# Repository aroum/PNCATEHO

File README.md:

<p align="center">
  <a href="https://github.com/aroum/PNCATEHO/tree/master/firmware">Firmware | </a>
  <a href="https://github.com/aroum/PNCATEHO/releases">Gerber | </a>
  <a href="../doc/socket.md">About socket</a>
</p>

---

## About

РИСАТЕНО (__RISATENO__) - created as a rethinking of [ARTSEY](https://artsey.io/) for the Russian language. 10 keys, two for each finger. The name is made up of letters on the main layer. The letters on the base layer are selected according to the. The original idea was to create a compact keyboard for chord typing, but it can also be used as a macro pad. When using two halves of РИСАТЕНО connected via Bluetooth, you can use the [Kladenets layout](https://ibnteo.github.io/kladenets/). But over time, PNCATEHO became something more. It is a synthesizer, a sampler, a MIDI keyboard, and a vast playground for your other experiments.

## Eras

Eras are a way to classify different versions of a project. The Stone Era reflects original ideas. The Glass Era reflects the community's desires and experiments with new switches. The Light Era illuminates the vision of the creators who use this project as a platform for professional growth and attempt what others were afraid to do.

| Name    | Alt Name  | Era   | Swtiches   | Hot-swap | LED              | Wireless | MCU           |
| ------- | --------- | ----- | ---------- | -------- | ---------------- | -------- | ------------- |
| V4      | -         | Stone | Choc V1    | ❌        | Per-key          | Optional | proMicro like |
| V5      | -         | Glass | Choc V1/V2 | ✅        | Per-key          | Optional | proMicro like |
| MK_Dose | Dozateno  | Glass | MK Dose/MX | ✅        | 3 Led indication | Optional | proMicro like |
| Welcome | Nizkoteno | Light | PG1316S    | ❌<br>    | Per-key          | ❌<br>    | rp2040        |

### Stone

The standard version of PNCATEHO from the Stone era. Supports per-key backlighting, the option to use a wireless controller with an external power switch and reset button, and an open case. It does not support hot-swapping switches and only supports Choc V1. [more about stone](stone/readme.md)

> [!WARNING]  
> In version 0.3 of the board there is a bug with the backlight on the right-hand half.

#### V0.3

#### 3D

### Glass

The modern era of PNCATEHO development. It differs from the Stone era in that it supports hot-swappable keys and ChocV1/V2, MK Dose, and MX switches. It also uses closed cases and a new design approach by turtle_bazon. [more about Glass](glass/readme.md)

> [!TIP]
> If you want to build a PNCATEHO with MX switches, you can use the PCB from MK Dose.

#### V5

#### MK_Dose

### Light

This is an era where the controller is soldered directly onto the PCB, exploring various form factors such as, for example, a PNCATEHO the size of a card. A project can become a flashlight, a development board, or even a portable gaming console. It all depends on the imagination of the community. The main contribution to this era has been made by the authors of the inpudiy community. [more about light](light/readme.md)

#### Welcome

## FAQ

### What is it for?

First and foremost, PNCATEHO is a fun project. It shouldn't be treated as an everyday keyboard—it’s more of a novelty, like a fridge magnet. That said, some people actually try to apply PNCATEHO's concepts to their daily-driver keyboards.

In many ways, the project served as a testing ground for experimenting with chording and exploring just how far you can minimize the number of keys. Of course, nothing stops you from using PNCATEHO as a macropad. There are also firmwares available to turn PNCATEHO into a sampler, synthesizer, or MIDI keyboard.

I wanted to design a layout that was simple and intuitive, yet still capable of acting as a near-full replacement for a standard keyboard. Unlike ARTSEY, I don’t use chords that require pressing more than two keys simultaneously. I also designed the layout based on letter frequency rather than just picking pleasant-sounding combinations. On top of that, I added two thumb keys—it felt odd to allocate two keys for every other finger while leaving the thumbs with nothing.

### Why PNCATEHO/RISATENO/РИСАТЕНО?

PNCATEHO is a loose transliteration of the Russian word "РИСАТЕНО" (RISATENO) into the Latin alphabet. The layout was designed based on letter frequency ([Wikipedia](https://ru.wikipedia.org/wiki/%D0%A7%D0%B0%D1%81%D1%82%D0%BE%D1%82%D0%BD%D0%BE%D1%81%D1%82%D1%8C)), where the first eight letters are four vowels ('И', 'А', 'Е', 'О') and four consonants ('Р', 'С', 'Т', 'Н'). To create a pronounceable name, they can be grouped into syllables: reading them one way gives __RISATENO__, and the other way gives __NOTESARI__ (options like "ONETASIR" were discarded as awkward-sounding). The second option felt a bit too "samurai," so I went with the first.

As a nice bonus, if you set aside the Cyrillic letter "И", the name transliterates perfectly into the Latin alphabet, and the letter "N" works great as a visual substitute for "И".

### Why no ergonomic stagger?

PNCATEHO was never meant to be an everyday keyboard—aesthetics take priority over ergonomics here, and in my opinion, ortholinear layouts look much cleaner. Besides, when you only have two keys per finger, column-staggering doesn't really make much of a difference anyway.

### How do you type on it?

Letter by letter, “dancing” your fingers to form chords. I tried to distribute chords by ease of pressing, so that the most common symbols use the simplest and most comfortable combinations. With some effort, you can learn all the common chords in a couple of days and, although slowly, fully type using just 10 keys with one hand.

It’s quite an unusual experience, especially if you’ve never used chords before. I strongly recommend printing the layout ([GitHub](https://github.com/aroum/PNCATEHO/tree/master/firmware)) and opening any beginner touch-typing app — even if you already know how to type on a regular keyboard, this will be a completely new and unique experience that you’ll likely never need anywhere else.

### Is this steno?

No, steno works completely differently ([example layout](https://github.com/openstenoproject/plover/files/247728/Russian.alphabet.and.layout.pdf)). It requires more keys and a different method. PNCATEHO, on the other hand, is letter-by-letter input based on frequency.

If you’re interested in steno, it’s worth starting with [Plover](https://www.openstenoproject.org/plover/).

## Inspiration

* [ARTSEY](https://artsey.io/)
* [The Paintbrush](https://github.com/artseyio/thepaintbrush)
* [Helix](https://github.com/MakotoKurauchi/helix)
* [wakizashi](https://klava.wiki/hypha/%D0%BA%D0%BB%D0%B0%D0%B2%D0%B8%D0%B0%D1%82%D1%83%D1%80%D1%8B/%D0%B2%D0%B0%D0%BA%D0%B8%D0%B4%D0%B7%D0%B0%D1%81%D0%B8) (saw after the release of PNCATEHO)

## Contribute list

* [aroum](https://github.com/aroum)
* [mayoroffk](https://github.com/mayoroffk)
* [turtle-bazon](https://github.com/turtle-bazon)
* [miwoho](https://github.com/miwoho)

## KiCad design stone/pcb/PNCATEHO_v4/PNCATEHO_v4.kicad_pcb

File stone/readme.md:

# STONE

The standard version of PNCATEHO from the Stone era. Supports per-key backlighting, the option to use a wireless controller with an external power switch and reset button, and an open case. It does not support hot-swapping switches and only supports Choc V1.

<p align="center">
  <a href="case/case_v4.stp">Case | </a>
  <a href="build.md">Build Guide</a>
</p>

## V0.3

### Features

* 10 keys, Kailh Choc V1 switches
* Choc spacing
* Direct pins
* Three mounting screws
* One PCB for right and left versions
* Wireless (optional)
* Per switch RGB (optional)
* Power switch for wireless controllers (optional)
* Two halves placed on one 100x100mm pcb (optional)

### PCB

There are several versions of the PCB. In version 0.3, the right half has an error in the LED footprints, so the backlighting can only be installed facing downward. This issue, along with other minor ones, was fixed in version 0.4.

For manufacturing, it is recommended to use 100×100 mm Gerber files. This way, 5 boards become 10 halves (5 right and 5 left).

### Case

In the case directory, there are two STEP files. case_v4.stp does not have cutouts for rubber feet, while case_v4_flex.stp includes 7 cutouts for rubber feet.

### Plate

No plate is needed for choc, but if you want you can order PCB or laser cut. These don't fit version 3 boards because you can't add screw cutouts.

### BOM

| Item                 | Quantity | Remarks                            |
| -------------------- | -------: | ---------------------------------- |
| nice!nano            |        1 | or any other compatible controller |
| Kailh Choc V1        |       10 | switches                           |
| Keycaps              |       10 | 1U                                 |
| YS-SK6812MINI-E      |       10 | RGB leds                           |
| Magnets              |      2-6 | disc 7x2 mm (for case)             |
| Sockets PH5.0mm      |     12x2 | for controller                     |
| SMD button 3x4x2mm   |        1 | for reset                          |
| MSK-12C02            |        1 | power switch  (wireless only)      |
| 301230 3.7v li-po    |        1 | battery  (wireless only)           |
| Silicone rubber feet |        7 | 5x2 mm                             |
| M2 nuts              |        3 | for case v3+                       |
| M2x4 sqrews          |        3 | for case v3+                       |

## 3D

### Case

The case folder contains a STEP file. The controller, circuitry, and mounting method are entirely up to you.

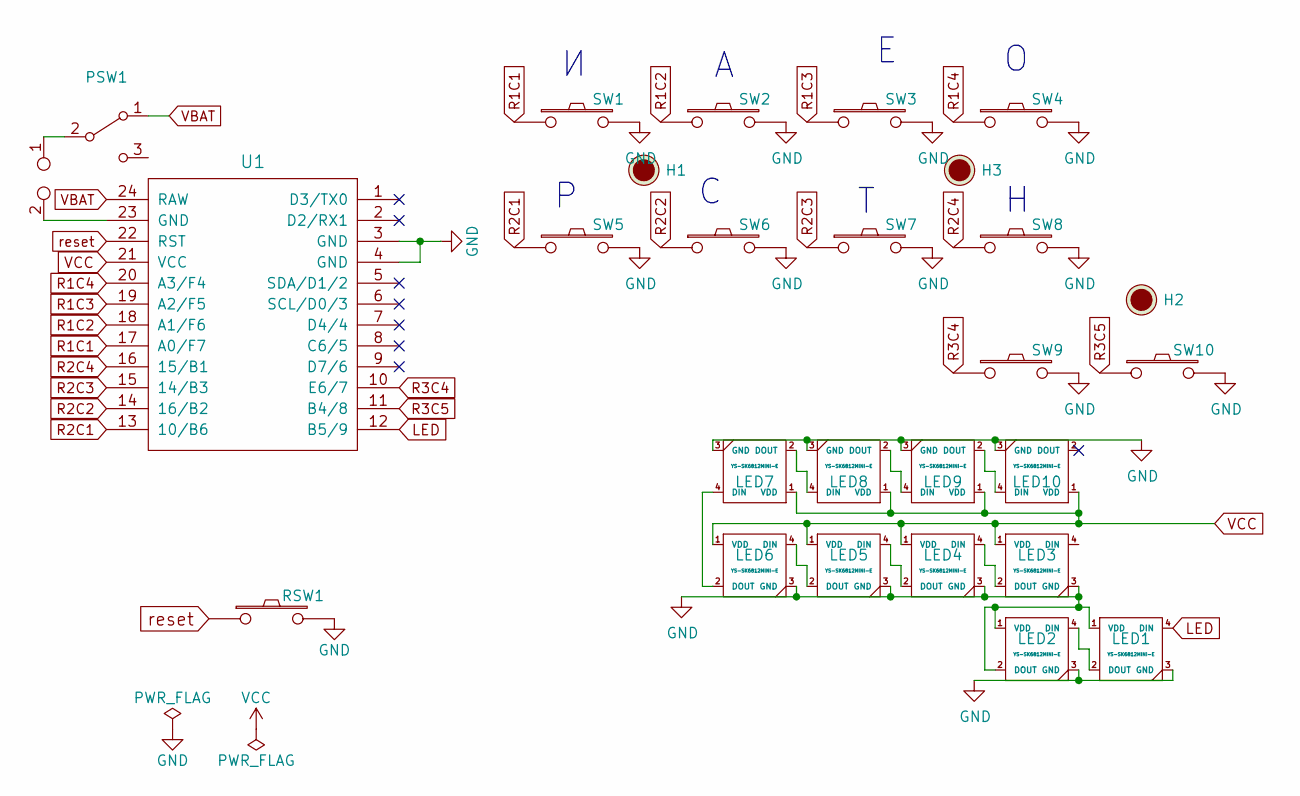
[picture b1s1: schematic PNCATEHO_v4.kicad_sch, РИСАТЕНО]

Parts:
H1, H2, H3: Hole; HOLE
J1: TestPoint_2Pole; battery_conn
LED1, LED2, LED3, LED4, LED5, LED6, LED7, LED8, LED9, LED10: YS-SK6812MINI-E; YS-SK6812MINI-E_duplex
PSW1: SW_SPDT; switch_MSK-12C02_smd
RSW1: SW_PUSH; SW_3x4x2_2legs_duplex
SW1, SW2, SW3, SW4, SW5, SW6, SW7, SW8, SW9, SW10: SW_PUSH; ChocV1_duplex
U1: ProMicro_r; ProMicro_duplex

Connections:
GND: LED1.1 (VDD), LED1.3 (GND), LED2.1 (VDD), LED2.2 (DOUT), LED2.3 (GND), LED3.3 (GND), LED4.3 (GND), LED5.3 (GND), LED6.3 (GND), LED7.3 (GND), LED8.3 (GND), LED9.3 (GND), LED10.3 (GND), RSW1.2, SW1.2, SW2.2, SW3.2, SW4.2, SW5.2, SW6.2, SW7.2, SW8.2, SW9.2, SW10.2, U1.3 (GND), U1.4 (GND)
LED: LED1.4 (DIN), U1.12 (B5/9)
unnamed: J1.2, U1.23 (GND)
unnamed: LED1.2 (DOUT), LED2.4 (DIN)
unnamed: LED3.2 (DOUT), LED4.4 (DIN)
unnamed: LED4.2 (DOUT), LED5.4 (DIN)
unnamed: LED5.2 (DOUT), LED6.4 (DIN)
unnamed: LED6.2 (DOUT), LED7.4 (DIN)
unnamed: LED7.2 (DOUT), LED8.4 (DIN)
unnamed: LED8.2 (DOUT), LED9.4 (DIN)
unnamed: LED9.2 (DOUT), LED10.4 (DIN)
unnamed: J1.1, PSW1.2 (B)
R1C1: SW1.1, U1.17 (A0/F7)
R1C2: SW2.1, U1.18 (A1/F6)
R1C3: SW3.1, U1.19 (A2/F5)
R1C4: SW4.1, U1.20 (A3/F4)
R2C1: SW5.1, U1.13 (10/B6)
R2C2: SW6.1, U1.14 (16/B2)
R2C3: SW7.1, U1.15 (14/B3)
R2C4: SW8.1, U1.16 (15/B1)
R3C4: SW9.1, U1.10 (E6/7)
R3C5: SW10.1, U1.11 (B4/8)
VBAT: PSW1.1 (A), U1.24 (RAW)
VCC: LED3.1 (VDD), LED4.1 (VDD), LED5.1 (VDD), LED6.1 (VDD), LED7.1 (VDD), LED8.1 (VDD), LED9.1 (VDD), LED10.1 (VDD), U1.21 (VCC)
reset: RSW1.1, U1.22 (RST)

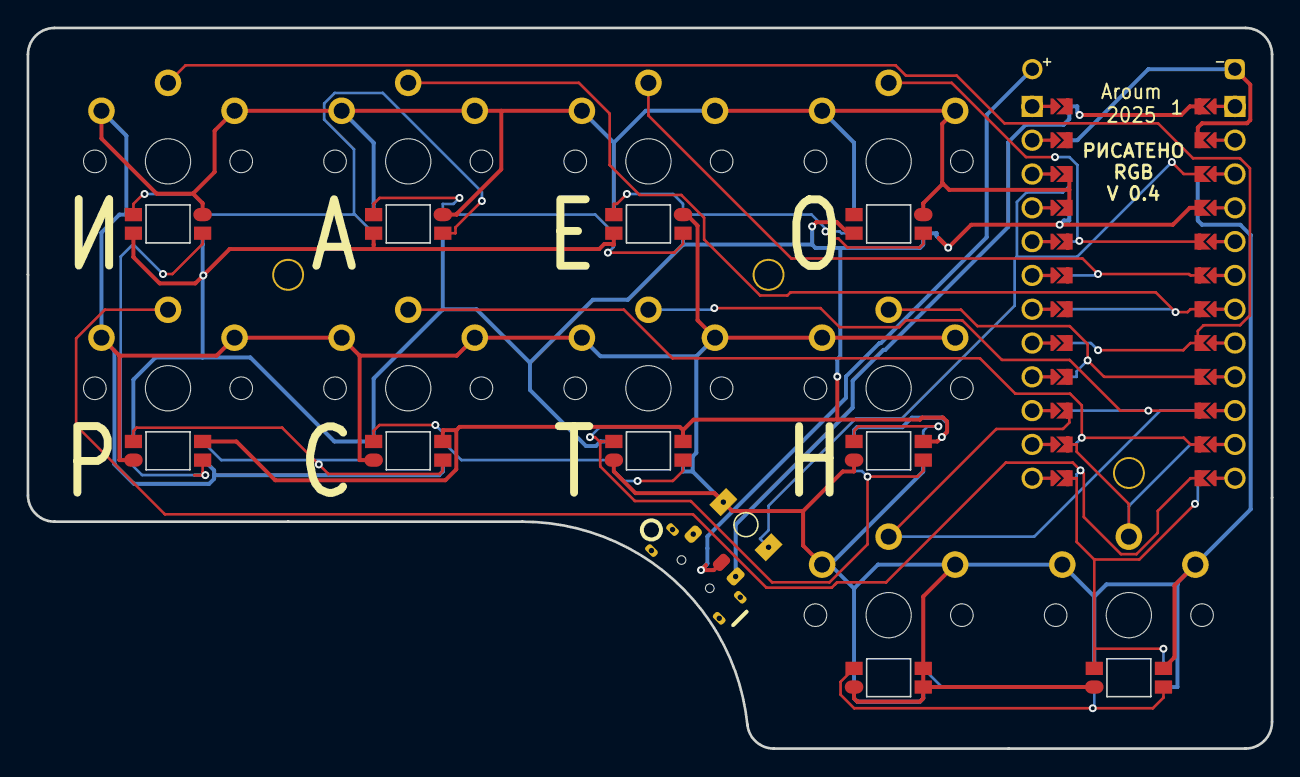
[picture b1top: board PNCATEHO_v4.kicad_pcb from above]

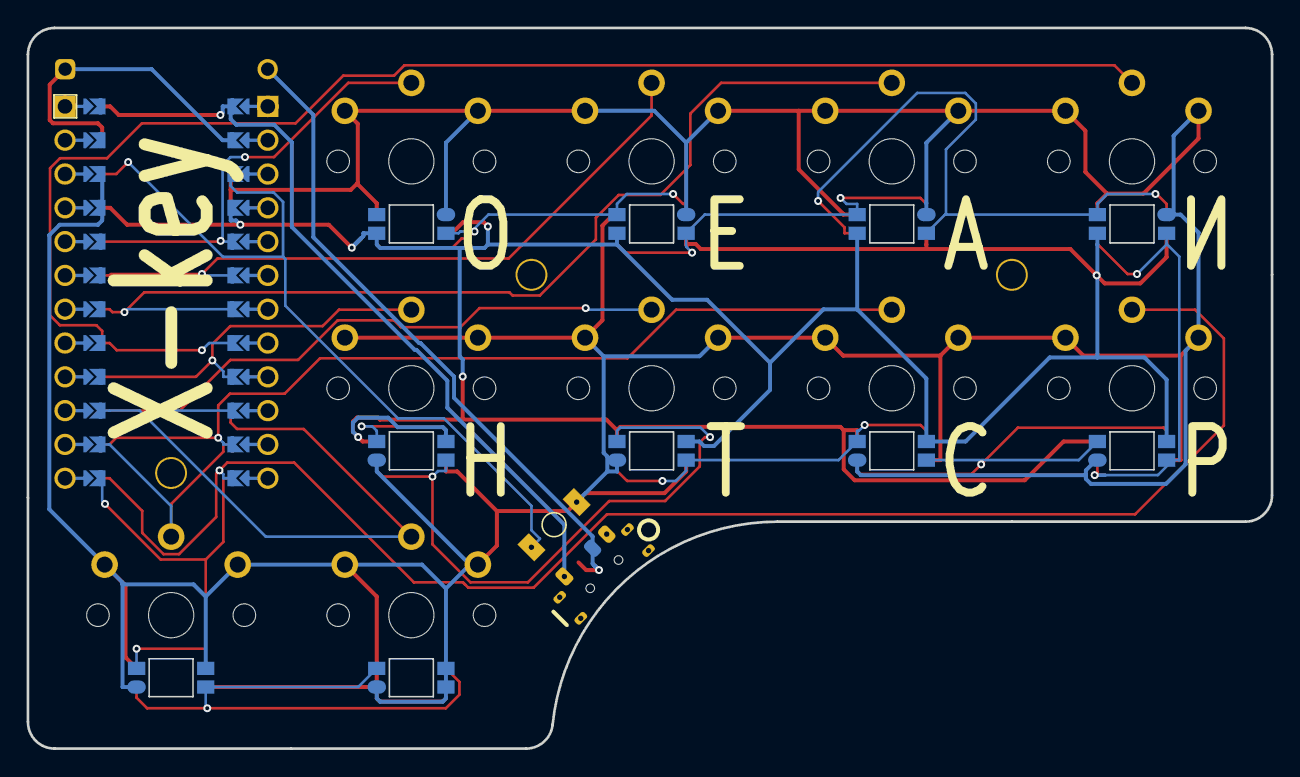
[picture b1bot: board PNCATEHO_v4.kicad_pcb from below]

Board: 2 copper layers, 93.5 x 54.1 mm, 27 parts (10 on the bottom side), 25 nets.

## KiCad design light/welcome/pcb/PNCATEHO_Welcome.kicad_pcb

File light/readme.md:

# light

This is an era where the controller is soldered directly onto the PCB, exploring various form factors such as, for example, a PNCATEHO the size of a card. A project can become a flashlight, a development board, or even a portable gaming console. It all depends on the imagination of the community. The main contribution to this era has been made by the authors of the inpudiy community.

## welcome (nizkoteno)

A credit card–sized RP2040-based PCB with a clean design, PG1316 low-profile switches, and integrated per-key RGB lighting.

<p align="center">
  <a href="https://htmlpreview.github.io/?https://github.com/inpudiy/PNCATEHO/blob/master/light/welcome/doc/ibom.html" style="text-decoration: none;">IBOM |</a>
  <a href="welcome/doc/schematic.pdf" style="text-decoration: none;"> Schematic PDF | </a>
  <a href="welcome/doc/build.md" style="text-decoration: none;"> Build guide</a>
</p>

### Features

* 10 low profile keys, PG1316 switches
* Debit card dimensions (ISO/IEC 7810 ID-1)
* Per switch WS2812 2020 led
* Soldered directly onto the RP2040 board
* ESD protection
* 16 MB flash memory
* cutout for a strap
* exposed 10-pin JST connector for connecting modules

### PCB

The current PCB version is v1.1. For ordering, specify a board thickness of 1.6 mm and a stencil for the top side of the board.

### JST

A BM10B-SRSS-TB connector is installed on the board. This is a 10-pin JST connector with a 1 mm pitch. The leftmost pin is connected to ground, and the rightmost pin provides 3.3V. Between them, the following GPIOs are exposed: 29, 28, 27, 26, 24, 21, 20, 19.

To run the controller, a stable 3.3V supply is required, while the RGB pins should receive 5V.

> [!WARNING]  
> DO NOT attempt to connect an external 3.3V supply while simultaneously powering the board via USB.

### Firmwares

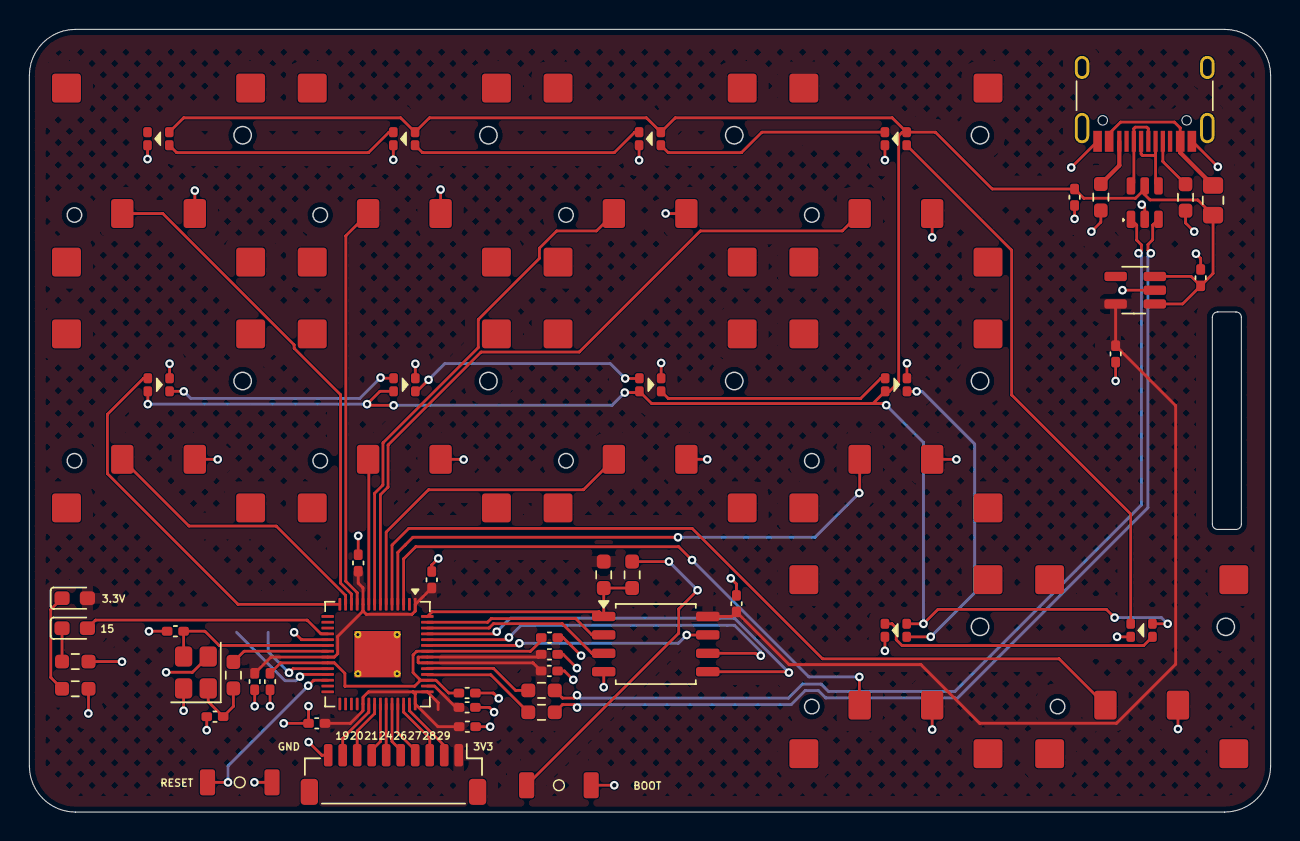
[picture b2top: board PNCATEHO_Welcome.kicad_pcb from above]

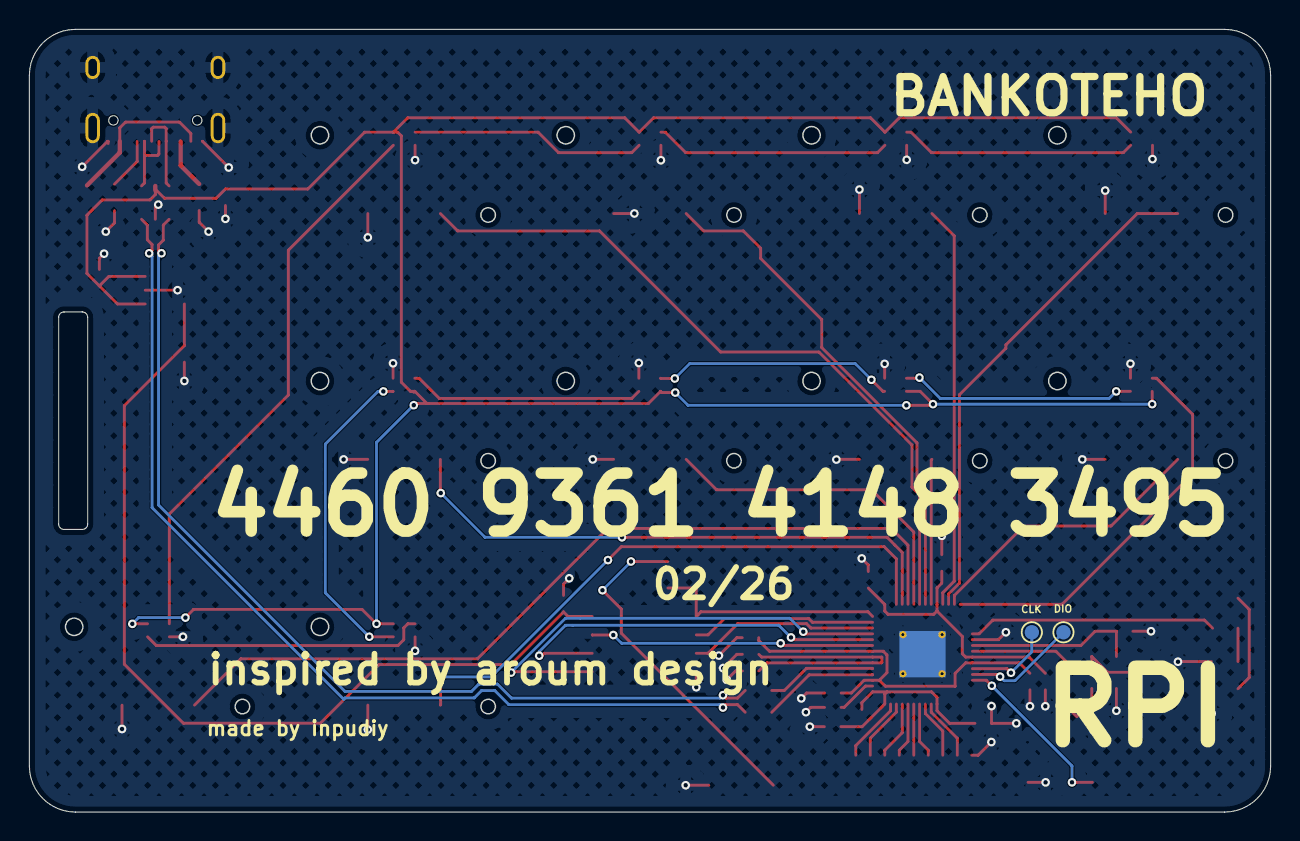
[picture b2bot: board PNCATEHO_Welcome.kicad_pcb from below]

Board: 2 copper layers, 85.6 x 54.0 mm, 60 parts (2 on the bottom side), 57 nets.

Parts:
C1, C2, C13, C16: 1uF; C_0402_1005Metric_Pad0.74x0.62mm_HandSolder
C3, C6, C7, C8, C9, C10, C11, C12, C14, C15, C17: 100nF; C_0402_1005Metric_Pad0.74x0.62mm_HandSolder
C4, C5: 15pF; C_0402_1005Metric_Pad0.74x0.62mm_HandSolder
D1: RED; LED_0603_1608Metric_Pad1.05x0.95mm_HandSolder
D2: BLUE; LED_0603_1608Metric_Pad1.05x0.95mm_HandSolder
D3, D4, D5, D6, D7, D8, D9, D10, D11, D12: LED-SMD_4P-L2.0-W1.8_XL-0807RGBC-WS2812B
F1: 0.5А 6V; Fuse_0805_2012Metric_Pad1.15x1.40mm_HandSolder
J1: USB_C_Receptacle_USB2.0; USB_C_Receptacle_HRO_TYPE-C-31-M-12
J2: Conn_01x10; JST_SH_BM10B-SRSS-TB_1x10-1MP_P1.00mm_Vertical
R1, R2: 5.1k; R_0603_1608Metric_Pad0.98x0.95mm_HandSolder
R3, R4, R9, R10: 1k; R_0603_1608Metric_Pad0.98x0.95mm_HandSolder
R5: 10k; R_0603_1608Metric_Pad0.98x0.95mm_HandSolder
R6, R7: 27; R_0603_1608Metric_Pad0.98x0.95mm_HandSolder
SW1, SW2, SW3, SW4, SW5, SW6, SW7, SW8, SW9, SW10: CPG1316S01D02-01
SW11: Boot; TS342A2P
SW12: Reset; TS342A2P
TP1, TP2: TestPoint; TestPoint_Pad_D1.0mm
U1: RP2040; QFN-56-1EP_7x7mm_P0.4mm_EP3.2x3.2mm_ThermalVias
U2: RT9013-33GB; SOT-23-5_HandSoldering
U3: W25Q128JVS; SOIC-8_5.3x5.3mm_P1.27mm
U4: USBLC6-2SC6; SOT23-6L
Y1: 12MHz; Crystal_SMD_Abracon_ABM8G-4Pin_3.2x2.5mm

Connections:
+1V1: C14.1, C15.1, C16.1, U1.23 (DVDD), U1.45 (VREG_VOUT), U1.50 (DVDD)
+3V3: C2.1, C3.1, C6.1, C7.1, C8.1, C9.1, C10.1, C11.1, C12.1, C13.1, D1.2 (A), J2.1, R5.2, U1.1 (IOVDD), U1.10 (IOVDD), U1.22 (IOVDD), U1.33 (IOVDD), U1.42 (IOVDD), U1.43 (ADC_AVDD), U1.44 (VREG_IN), U1.48 (USB_VDD), U1.49 (IOVDD), U2.5 (VOUT), U3.8 (VCC)
+5V: C1.1, C17.2, D3.4 (VDD), D4.4 (VDD), D5.4 (VDD), D6.4 (VDD), D7.4 (VDD), D8.4 (VDD), D9.4 (VDD), D10.4 (VDD), D11.4 (VDD), D12.4 (VDD), F1.2, U2.1 (VIN), U2.3 (EN), U4.5 (VBUS)
BOOT: R4.2, SW11.2
GND: C1.2, C2.2, C3.2, C4.2, C5.2, C6.2, C7.2, C8.2, C9.2, C10.2, C11.2, C12.2, C13.2, C14.2, C15.2, C16.2, C17.1, D3.2 (GND), D4.2 (GND), D5.2 (GND), D6.2 (GND), D7.2 (GND), D8.2 (GND), D9.2 (GND), D10.2 (GND), D11.2 (GND), D12.2 (GND), J1.A1 (GND), J1.A12 (GND), J1.B1 (GND), J1.B12 (GND), J1.S1 (SHIELD), J2.10, R1.2, R2.2, R9.1, R10.1, SW1.2, SW2.2, SW3.2, SW4.2, SW5.2, SW6.2, SW7.2, SW8.2, SW9.2, SW10.2, SW11.1, SW12.1, U1.19 (TESTEN), U1.57 (GND), U2.2 (GND), U3.4 (GND), U4.2 (GND), Y1.2, Y1.4
GPIO19: J2.9, U1.34 (GPIO22)
GPIO20: J2.8, U1.35 (GPIO23)
GPIO21: J2.7, U1.36 (GPIO24)
GPIO24: J2.6, U1.37 (GPIO25)
GPIO26: J2.5, U1.38 (GPIO26_ADC0)
GPIO27: J2.4, U1.39 (GPIO27_ADC1)
GPIO28: J2.3, U1.40 (GPIO28_ADC2)
GPIO29: J2.2, U1.41 (GPIO29_ADC3)
LED: D3.3 (DI), U1.14 (GPIO11)
N: R7.2, U1.46 (USBD_N)
unnamed: C5.1, R3.1, Y1.1
unnamed: D1.1 (K), R9.2
unnamed: D2.1 (K), R10.2
unnamed: D3.1 (DO), D4.3 (DI)
unnamed: D4.1 (DO), D5.3 (DI)
unnamed: D5.1 (DO), D6.3 (DI)
unnamed: D6.1 (DO), D7.3 (DI)
unnamed: D7.1 (DO), D8.3 (DI)
unnamed: D8.1 (DO), D9.3 (DI)
unnamed: D9.1 (DO), D10.3 (DI)
unnamed: D10.1 (DO), D11.3 (DI)
unnamed: D11.1 (DO), D12.3 (DI)
unnamed: F1.1, J1.A4 (VBUS), J1.A9 (VBUS), J1.B4 (VBUS), J1.B9 (VBUS)
unnamed: J1.A5 (CC1), R1.1
unnamed: J1.B5 (CC2), R2.1
P: R6.2, U1.47 (USBD_P)
QSPI_CS: R4.1, R5.1, U1.56 (QSPI_SS), U3.1 (~CS)
QSPI_D0: U1.53 (QSPI_SD0), U3.5 (DI(IO0))
QSPI_D1: U1.55 (QSPI_SD1), U3.2 (DO(IO1))
QSPI_D2: U1.54 (QSPI_SD2), U3.3 (IO2)
QSPI_D3: U1.51 (QSPI_SD3), U3.7 (IO3)
QSPI_SCLK: U1.52 (QSPI_SCLK), U3.6 (CLK)
R1C1: SW1.1, U1.12 (GPIO9)
R1C2: SW2.1, U1.11 (GPIO8)
R1C3: SW3.1, U1.8 (GPIO6)
R1C4: SW4.1, U1.7 (GPIO5)
R2C1: SW5.1, U1.13 (GPIO10)
R2C2: SW6.1, U1.9 (GPIO7)
R2C3: SW7.1, U1.6 (GPIO4)
R2C4: SW8.1, U1.4 (GPIO2)
R3C4: SW9.1, U1.3 (GPIO1)
R3C5: SW10.1, U1.5 (GPIO3)
STATE_LED: D2.2 (A), U1.18 (GPIO15)
SWCLK: TP1.1 (1_1), U1.24 (SWCLK)
SWDIO: TP2.1 (1_1), U1.25 (SWD)
USBD+: J1.A6 (D+), J1.B6 (D+), U4.6 (I/O1)
USBD-: J1.A7 (D-), J1.B7 (D-), U4.4 (I/O2)
USBD_N: R7.1, U4.3 (I/O2)
USBD_P: R6.1, U4.1 (I/O1)
XIN: C4.1, U1.20 (XIN), Y1.3
XOUT: R3.2, U1.21 (XOUT)
~RESET: SW12.2, U1.26 (RUN)

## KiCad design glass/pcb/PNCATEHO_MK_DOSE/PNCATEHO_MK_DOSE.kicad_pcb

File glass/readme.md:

# glass

The modern era of PNCATEHO development. It differs from the Stone era in that it supports hot-swappable keys and ChocV1/V2, MK Dose, and MX switches. It also uses closed cases and a new design approach by turtle_bazon.

## v5

An updated version of the PCB by turtle_bazon. It retains the core features of the Stone era, while adding support for Choc V2, as well as hot-swappable switches, an enclosed case, and a PCB with a more refined design.

<p align="center">
  <a href="case/v5/">Case | </a>
  <a href="build_v5.md">Build Guide</a>
</p>

### Features

* 10 keys, Kailh Choc **V1/V2** switches
* **Hot-Swap Socket**
* MX spacing
* Direct pins
* Three mounting screws
* One PCB for right and left versions
* Wireless (optional)
* Per switch RGB (optional)
* Power switch for wireless controllers (optional)
* Two halves placed on one 100x100mm pcb (optional)

### PCB

The current PCB version is 0.5.2. For manufacturing, it is recommended to use 100×100 mm Gerber files. This way, 5 boards become 10 halves (with an extra cute keychain in between).

### Case

To assemble the case, you need to print the following files:

* PNCATEHO_MK_DOSE-case-bottom-left - top part of the case
* PNCATEHO_MK_DOSE-case-top-left.step -  bottom part of the case
* PNCATEHO_MK_DOSE-reset-button-pusher.step - reset button actuator
* PNCATEHO_MK_DOSE-case-top-cover-blank-left - controller cover

There are also different versions of the controller cover with katakana or lp. Additionally, the case [directory](../glass/case/MK_DOSE) includes an editable FreeCAD file: **PNCATEHO_v5.FCStd**.

### BOM

| Item                                 | Quantity | Remarks                                      |
| ------------------------------------ | -------: | -------------------------------------------- |
| nice!nano                            |        1 | or any other pro micro compatible controller |
| Kailh Choc V1/2                      |       10 | switches                                     |
| Hot swap sockets                     |       10 | CPG135001S30                                 |
| YS-SK6812MINI-E                      |       10 | RGB leds                                     |
| Machine Pin Socket with 2.54mm pitch |     12x2 | for controller                               |
| RGB Led pin or brass wire            |     12x2 | for pin header                               |
| SMD button 3x4x2mm                   |        1 | for reset                                    |
| MSK-12C02                            |        1 | power switch  (wireless only)                |
| 301230 3.7v li-po                    |        1 | battery  (wireless only)                     |
| Silicone rubber feet                 |        5 | 10x2 mm                                      |
| M2х6 screw                           |        3 | for case                                     |
| Keycaps                              |       10 | 1U                                           |

## MK Dose (dozateno)

A version of the PCB designed for MK Dose format switches. It also supports standard MX switches. It differs by lacking per-switch backlighting, but includes indication using three SMD LEDs. Like V5, it features an enclosed case available in several variations.

<p align="center">
  <a href="case/MK_DOSE/">Case | </a>
  <a href="build_mkdose.md">Build Guide</a>
</p>

### Features

* 10 keys, MK Dose/MX switches
* 3 Led indication
* **Hot-Swap Socket**
* MX spacing
* Three mounting screws
* One PCB for right and left versions
* Wireless (optional)
* Power switch for wireless controllers (optional)
* Two halves placed on one 100x100mm pcb (optional)

### PCB

it is recommended to use 100×100 mm Gerber files. This way, 5 boards become 10 halves (with an extra cute keychain in between).

### Case

To assemble the case, you need to print the following files:

* PNCATEHO_v5-bottom-case-left - top part of the case
* PNCATEHO_v5-top-case-left.step -  bottom part of the case
* PNCATEHO_v5-power-switch-pusher.step - power switch actuator
* PNCATEHO_v5-reset-button-pusher.step - reset button actuator
* PNCATEHO_v5-top-cover-left-blank.step - controller cover

There are also different versions of the controller cover with the **PNCATEHO** label in *ReggageOne* or *RubikMonoOne* fonts.
Additionally, the case [directory](../glass/case/v5) includes an editable FreeCAD file: **PNCATEHO_MK_DOSE.FCStd*.

### BOM

| Item                                 | Quantity | Remarks                                      |
| ------------------------------------ | -------: | -------------------------------------------- |
| nice!nano                            |        1 | or any other pro micro compatible controller |
| MK Dose or MX Swtich                 |       10 | switches                                     |
| Hot swap sockets                     | 10 or 20 | CPG151101S11                                 |
| Diode 1N4148W                        | 10 or 20 | for matrix                                   |
| 0603 led                             |        3 | for indication                               |
| 0603 1-10k resitsor                  |        3 | for led                                      |
| Machine Pin Socket with 2.54mm pitch |     12x2 | for controller                               |
| RGB Led pin or brass wire            |     12x2 | for pin header                               |
| SMD button 3x4x2mm                   |        1 | for reset                                    |
| BSI-10H                              |        1 | power switch  (wireless only)                |
| 301230 3.7v li-po                    |        1 | battery  (wireless only)                     |
| Silicone rubber feet                 |        5 | 8x2 mm                                       |
| m2х8 screw                           |        3 | for case                                     |
| Keycaps                              |       10 | 1U                                           |

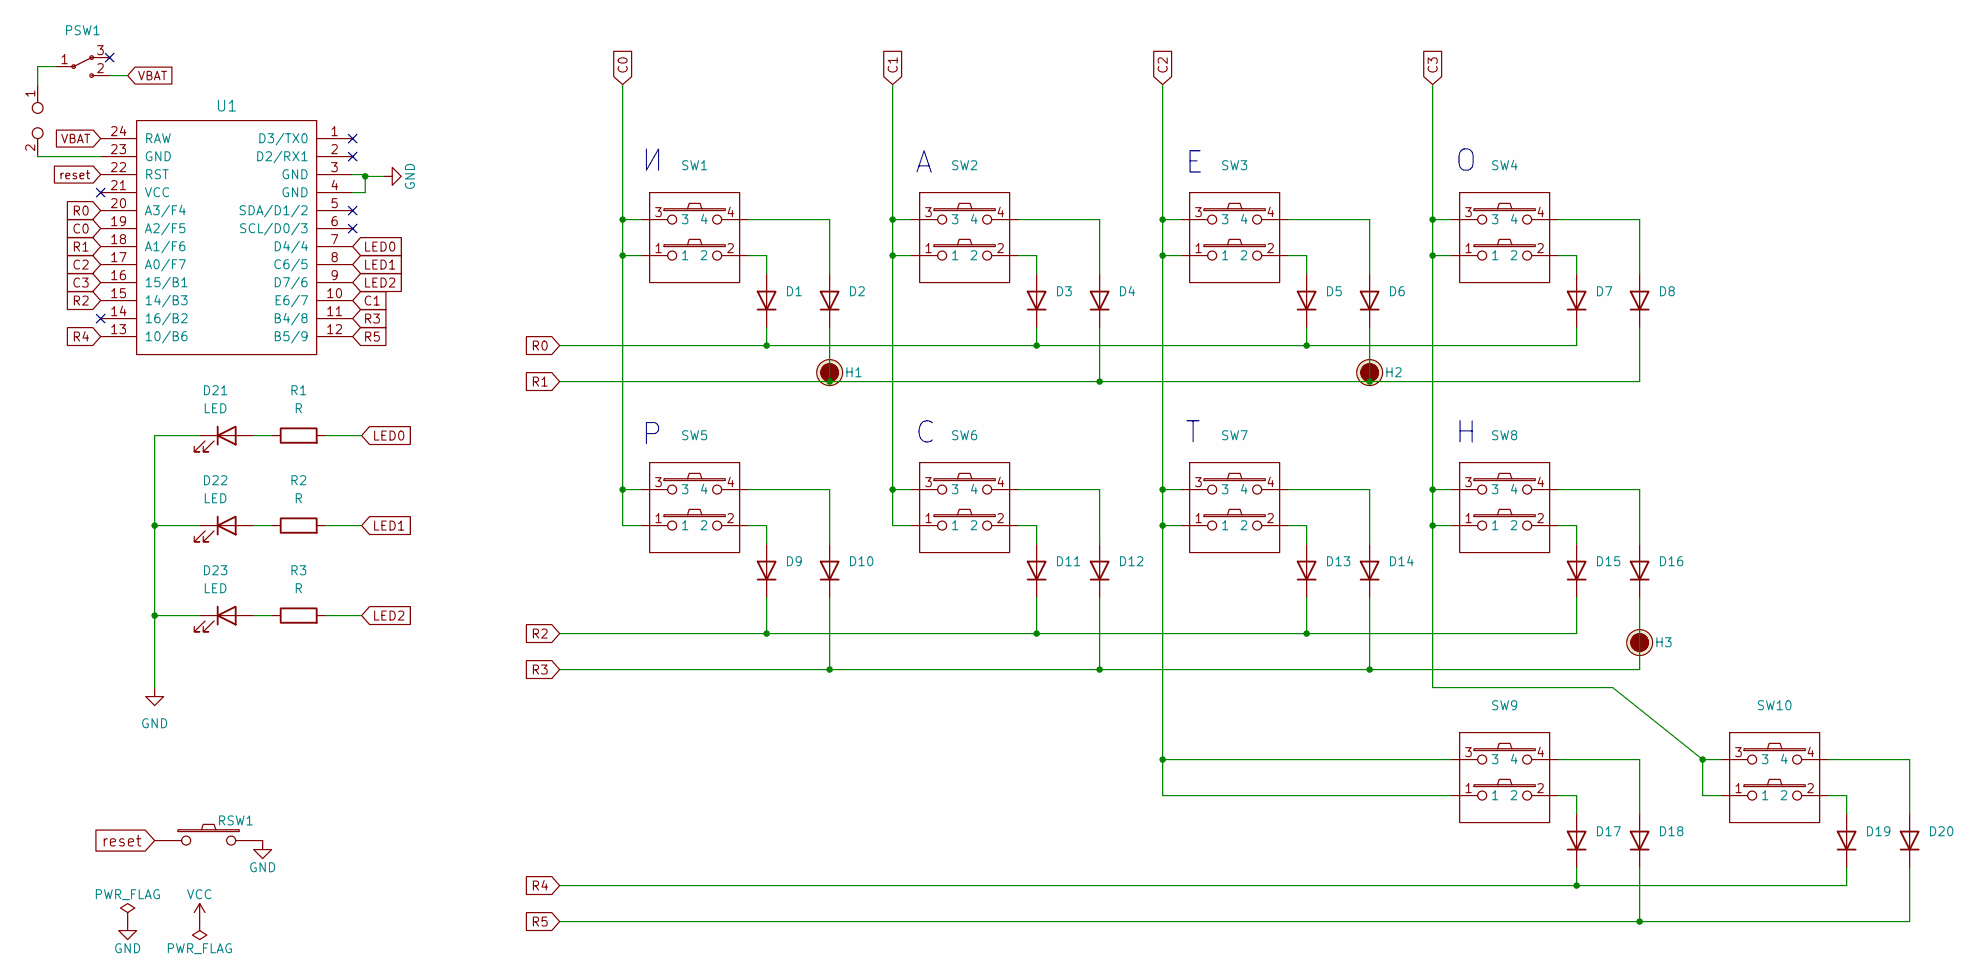
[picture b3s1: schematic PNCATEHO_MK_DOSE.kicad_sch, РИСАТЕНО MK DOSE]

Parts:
D1, D2, D3, D4, D5, D6, D7, D8, D9, D10, D11, D12, D13, D14, D15, D16, D17, D18, D19, D20: 1N4148W; D3_SMD
D21, D22, D23: LED; 0603-led_dual
H1, H2, H3: Hole
J1: TestPoint_2Pole; battery_conn_duplex
PSW1: bsi10h
R1, R2, R3: R; 0603-resistor_dual
RSW1: SW_PUSH; SW_3x4x2_2legs_duplex
SW1, SW2, SW3, SW4, SW5, SW6, SW7, SW8, SW9, SW10: MK-DOSE
U1: ProMicro_r; ProMicro_duplex_mirrored

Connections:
C0: SW1.1, SW1.3, SW5.1, SW5.3, U1.19 (A2/F5)
C1: SW2.1, SW2.3, SW6.1, SW6.3, U1.10 (E6/7)
C2: SW3.1, SW3.3, SW7.1, SW7.3, SW9.1, SW9.3, U1.17 (A0/F7)
C3: SW4.1, SW4.3, SW8.1, SW8.3, SW10.1, SW10.3, U1.16 (15/B1)
GND: D21.1 (K), D22.1 (K), D23.1 (K), RSW1.2, U1.3 (GND), U1.4 (GND)
LED0: R1.2, U1.7 (D4/4)
LED1: R2.2, U1.8 (C6/5)
LED2: R3.2, U1.9 (D7/6)
unnamed: D1.2 (A), SW1.2
unnamed: D2.2 (A), SW1.4
unnamed: D3.2 (A), SW2.2
unnamed: D4.2 (A), SW2.4
unnamed: D5.2 (A), SW3.2
unnamed: D6.2 (A), SW3.4
unnamed: D7.2 (A), SW4.2
unnamed: D8.2 (A), SW4.4
unnamed: D9.2 (A), SW5.2
unnamed: D10.2 (A), SW5.4
unnamed: D11.2 (A), SW6.2
unnamed: D12.2 (A), SW6.4
unnamed: D13.2 (A), SW7.2
unnamed: D14.2 (A), SW7.4
unnamed: D15.2 (A), SW8.2
unnamed: D16.2 (A), SW8.4
unnamed: D17.2 (A), SW9.2
unnamed: D18.2 (A), SW9.4
unnamed: D19.2 (A), SW10.2
unnamed: D20.2 (A), SW10.4
unnamed: D21.2 (A), R1.1
unnamed: D22.2 (A), R2.1
unnamed: D23.2 (A), R3.1
unnamed: J1.1, PSW1.1
unnamed: J1.2, U1.23 (GND)
R0: D1.1 (K), D3.1 (K), D5.1 (K), D7.1 (K), U1.20 (A3/F4)
R1: D2.1 (K), D4.1 (K), D6.1 (K), D8.1 (K), U1.18 (A1/F6)
R2: D9.1 (K), D11.1 (K), D13.1 (K), D15.1 (K), U1.15 (14/B3)
R3: D10.1 (K), D12.1 (K), D14.1 (K), D16.1 (K), U1.11 (B4/8)
R4: D17.1 (K), D19.1 (K), U1.13 (10/B6)
R5: D18.1 (K), D20.1 (K), U1.12 (B5/9)
VBAT: PSW1.2, U1.24 (RAW)
reset: RSW1.1, U1.22 (RST)

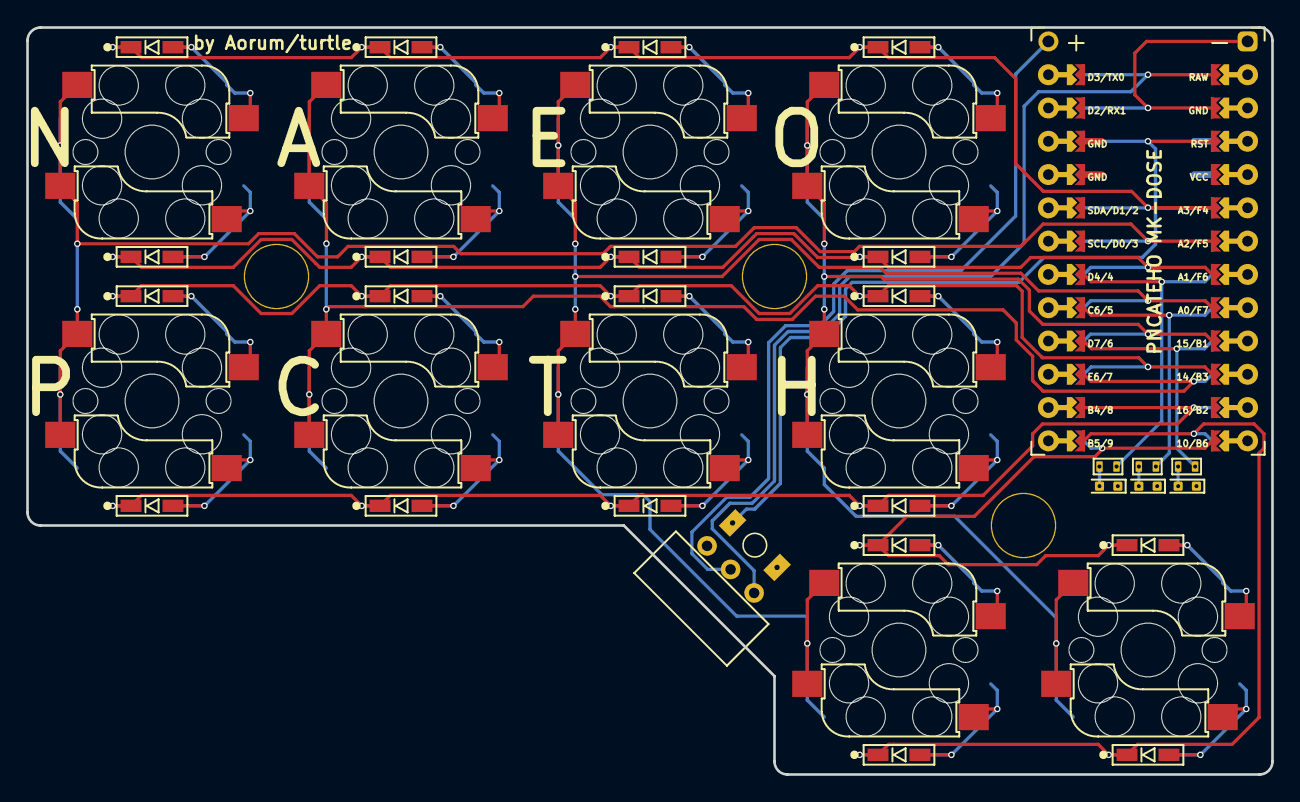
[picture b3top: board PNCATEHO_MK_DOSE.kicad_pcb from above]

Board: 2 copper layers, 95.0 x 57.0 mm, 43 parts (0 on the bottom side), 41 nets.

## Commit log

2021-08-10 init commit
2021-08-12 now double-sided PCB
    double-sided PCB
    add non RGB option
    update README.md
    remove gerber from code
2021-08-29 Update README.md
    add Build guide
2021-12-04 add: case, plate, firmware
2021-12-09 deleting unnecessary files
2022-01-01 Added interactive BOM, fixed QMK config
2022-08-18 rename folder
2022-12-12 Update QMK config for new QMK version
2023-10-15 v3
    * Power switch for wireless controllers(optional)
    * Two halves inscribed in 100x100 mm(optional)
    * Three mounting screws
    * One PCB for right and left versions
2024-01-09 fix title
2024-01-09 fix ibom
2024-01-09 fix ibom 2
2024-01-09 remove production dir, u[date readme for plate
2024-02-07 Add Vial firmware
2025-02-25 Initial footprint change for HS chocs
2025-03-02 Library change, change to hs switches, led changes
2025-03-02 Almosta all routed
2025-03-04 moved to PNCATEHO_v5
2025-03-04 Added legacy libs
2025-03-04 Deleted v4 project files
2025-03-05 Basic layout
2025-03-06 v5 ready for production?
2025-03-06 MK-DOSE initial
2025-03-07 Changed vias to 0.3/0.5
2025-03-24 PNCATEHO MK-DOSE routed
2025-03-24 Update library
2025-03-28 MK-DOSE version panel
2025-03-29 Change pads to edge cuts in separator elements
2025-03-29 Change user.eco layouting to produce switch placeholder on export
2025-03-29 Small beauty fix
2025-03-31 v0.5.1 100x100 version pcb
2025-03-31 Ignore MK_DOSE production
2025-04-03 v5 100x100 version
2025-04-03 MK-DOSE version, with 100x100 version
2025-04-03 Some production fixes
2025-04-23 Diode footprint update. Some changes.
2025-04-24 Fix text positions
2025-04-29 Nanoteno on 100x100
2025-04-30 Nanoteno with letters
2025-05-01 Fixes
2025-05-06 v4
    * Added controller jumpers
    + No need to flip the controller anymore
    * Fixed RGB lighting on the right half
    * Increased case clearances by 0.2 mm for better FDM printing
    - Removed copper pour from the PCB
2025-05-20 v5 case
2025-05-20 Readme for v5
2025-05-20 Assembly render
2025-05-20 Fix typo on v5 readme
2025-05-20 Fix another v5 readme typo
2025-05-20 Add jumper soldering in build guide
2025-05-23 Copy PNCATEHO v5 and MK_DOSE
2025-05-23 Project structure reorganization
2025-05-23 Add light era readme
2025-05-23 Fix ligh readme link
2025-05-23 Add glass era readme
2025-05-23 v5 readme fixes
2025-05-23 v5 table fix
2025-05-23 Fix v5 readme
2025-05-23 Add note for magnets
2025-05-26 Subheaders for images of v5 and MK_DOSE
2025-07-10 Change led pin to TX0
2025-07-12 Added firmware section.
2025-07-12 Added pin headers soldering helpers
2025-08-12 MK_DOSE case
2025-08-12 MK_DOSE case sources
2025-08-23 Change default Silicone Pad Diameter to 8mm
2025-09-07 Parametrized cover height and lp variant exports
2026-05-25 Full project import from fork
2026-06-06 Add firmware packages and update docs
    Add multiple firmware targets and KLE layouts (QMK, Vial, ZMK, RMK, MIDI, pra32-u and KLE JSON/PNG/PDF assets) including keymaps, configs, macros and info files for pncateho. Update README copy and e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
2026-06-06 Update Welcome era switch type in README
    Correct the Welcome era table entry to use PG1316S instead of ULP in README.md. This fixes an incorrect switch model shown in the project overview.
